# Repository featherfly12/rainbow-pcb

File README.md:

This is a pcb strip with rainbow leds! The part list is below and all the kicad files are listed\
you can buy assembled from vendor or try to solder it yourself!

## Parts List (BOM)

| Component | Value/Spec | Package | Qty |
|---|---|---|---|
| J1 — DC barrel jack | 5.5×2.1mm | THT | 1 |
| D1 — Protection diode | Schottky, SS14 | SOD-123 | 1 |
| SW1 — Switch | SPST, maintained | THT or SMD | 1 |
| LED — red | Vf ≈ 2.0V | 0805 | 13 |
| LED — orange | Vf ≈ 2.1V | 0805 | 13 |
| LED — yellow | Vf ≈ 2.1V | 0805 | 13 |
| LED — green | Vf ≈ 3.0V | 0805 | 13 |
| LED — blue | Vf ≈ 3.2V | 0805 | 13 |
| LED — purple | Vf ≈ 3.2V | 0805 | 13 |
| LED — pink | Vf ≈ 3.0-3.2V | 0805 | 13 |
| Resistor — 180Ω (red strings) | 180Ω | 0805 | 13 |
| Resistor — 160Ω (orange strings) | 160Ω | 0805 | 13 |
| Resistor — 160Ω (yellow strings) | 160Ω | 0805 | 13 |
| Resistor — 110Ω (green strings) | 110Ω | 0805 | 13 |
| Resistor — 100Ω (blue strings) | 100Ω | 0805 | 13 |
| Resistor — 100Ω (purple strings) | 100Ω | 0805 | 13 |
| Resistor — 100Ω (pink strings) | 100Ω | 0805 | 13 |
| Wall adapter | Regulated 5V/2A, center-positive | — | 1 |

**Total: 91 LEDs, 91 resistors, 1 jack, 1 diode, 1 switch**

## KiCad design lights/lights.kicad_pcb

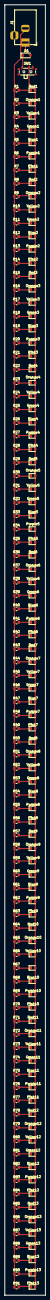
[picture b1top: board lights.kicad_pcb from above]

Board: 2 copper layers, 17.2 x 547.5 mm, 185 parts (0 on the bottom side), 95 nets.

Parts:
Blue1, Blue2, Blue3, Blue4, Blue5, Blue6, Blue7, Blue8, Blue9, Blue10, Blue11, Blue12, Blue13: LED; LED_0805_2012Metric
D1: D_Schottky; D_SOD-123
Green1, Green2, Green3, Green4, Green5, Green6, Green7, Green8, Green9, Green10, Green11, Green12, Green13: LED; LED_0805_2012Metric
J1: Barrel_Jack; BarrelJack_Horizontal
Orange1, Orange2, Orange3, Orange4, Orange5, Orange6, Orange7, Orange8, Orange9, Orange10, Orange11, Orange12, Orange13: LED; LED_0805_2012Metric
Pink1, Pink2, Pink3, Pink4, Pink5, Pink6, Pink7, Pink8, Pink9, Pink10, Pink11, Pink12, Pink13: LED; LED_0805_2012Metric
Purple1, Purple2, Purple3, Purple4, Purple5, Purple6, Purple7, Purple8, Purple9, Purple10, Purple11, Purple12, Purple13: LED; LED_0805_2012Metric
R1, R2, R3, R4, R5, R6, R7, R8, R9, R10, R11, R12, R13, R14, R15, R16, R17, R18, R19, R20, R21, R22, R23, R24, R25, R26, R27, R28, R29, R30, R31, R32, R33, R34, R35, R36, R37, R38, R39, R40, R41, R42, R43, R44, R45, R46, R47, R48, R49, R50, R51, R52, R53, R54, R55, R56, R57, R58, R59, R60, R61, R62, R63, R64, R65, R66, R67, R68, R69, R70, R71, R72, R73, R74, R75, R76, R77, R78, R79, R80, R81, R82, R83, R84, R85, R86, R87, R88, R89, R90, R91: R; R_0805_2012Metric
Red1, Red2, Red3, Red4, Red5, Red6, Red7, Red8, Red9, Red10, Red11, Red12, Red13: LED; LED_0805_2012Metric
SW1: SW_SPST; SW_SPDT_PCM12
Yellow1, Yellow2, Yellow3, Yellow4, Yellow5, Yellow6, Yellow7, Yellow8, Yellow9, Yellow10, Yellow11, Yellow12, Yellow13: LED; LED_0805_2012Metric

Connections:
/+5V: Blue1.2 (A), Blue2.2 (A), Blue3.2 (A), Blue4.2 (A), Blue5.2 (A), Blue6.2 (A), Blue7.2 (A), Blue8.2 (A), Blue9.2 (A), Blue10.2 (A), Blue11.2 (A), Blue12.2 (A), Blue13.2 (A), Green1.2 (A), Green2.2 (A), Green3.2 (A), Green4.2 (A), Green5.2 (A), Green6.2 (A), Green7.2 (A), Green8.2 (A), Green9.2 (A), Green10.2 (A), Green11.2 (A), Green12.2 (A), Green13.2 (A), Orange1.2 (A), Orange2.2 (A), Orange3.2 (A), Orange4.2 (A), Orange5.2 (A), Orange6.2 (A), Orange7.2 (A), Orange8.2 (A), Orange9.2 (A), Orange10.2 (A), Orange11.2 (A), Orange12.2 (A), Orange13.2 (A), Pink1.2 (A), Pink2.2 (A), Pink3.2 (A), Pink4.2 (A), Pink5.2 (A), Pink6.2 (A), Pink7.2 (A), Pink8.2 (A), Pink9.2 (A), Pink10.2 (A), Pink11.2 (A), Pink12.2 (A), Pink13.2 (A), Purple1.2 (A), Purple2.2 (A), Purple3.2 (A), Purple4.2 (A), Purple5.2 (A), Purple6.2 (A), Purple7.2 (A), Purple8.2 (A), Purple9.2 (A), Purple10.2 (A), Purple11.2 (A), Purple12.2 (A), Purple13.2 (A), Red1.2 (A), Red2.2 (A), Red3.2 (A), Red4.2 (A), Red5.2 (A), Red6.2 (A), Red7.2 (A), Red8.2 (A), Red9.2 (A), Red10.2 (A), Red11.2 (A), Red12.2 (A), Red13.2 (A), SW1.2 (B), Yellow1.2 (A), Yellow2.2 (A), Yellow3.2 (A), Yellow4.2 (A), Yellow5.2 (A), Yellow6.2 (A), Yellow7.2 (A), Yellow8.2 (A), Yellow9.2 (A), Yellow10.2 (A), Yellow11.2 (A), Yellow12.2 (A), Yellow13.2 (A)
GND: J1.2, R1.1, R2.1, R3.1, R4.1, R5.1, R6.1, R7.1, R8.1, R9.1, R10.1, R11.1, R12.1, R13.1, R14.1, R15.1, R16.1, R17.1, R18.1, R19.1, R20.1, R21.1, R22.1, R23.1, R24.1, R25.1, R26.1, R27.1, R28.1, R29.1, R30.1, R31.1, R32.1, R33.1, R34.1, R35.1, R36.1, R37.1, R38.1, R39.1, R40.1, R41.1, R42.1, R43.1, R44.1, R45.1, R46.1, R47.1, R48.1, R49.1, R50.1, R51.1, R52.1, R53.1, R54.1, R55.1, R56.1, R57.1, R58.1, R59.1, R60.1, R61.1, R62.1, R63.1, R64.1, R65.1, R66.1, R67.1, R68.1, R69.1, R70.1, R71.1, R72.1, R73.1, R74.1, R75.1, R76.1, R77.1, R78.1, R79.1, R80.1, R81.1, R82.1, R83.1, R84.1, R85.1, R86.1, R87.1, R88.1, R89.1, R90.1, R91.1
unnamed: Blue1.1 (K), R5.2
unnamed: Blue2.1 (K), R12.2
unnamed: Blue3.1 (K), R19.2
unnamed: Blue4.1 (K), R26.2
unnamed: Blue5.1 (K), R33.2
unnamed: Blue6.1 (K), R40.2
unnamed: Blue7.1 (K), R47.2
unnamed: Blue8.1 (K), R54.2
unnamed: Blue9.1 (K), R61.2
unnamed: Blue10.1 (K), R68.2
unnamed: Blue11.1 (K), R75.2
unnamed: Blue12.1 (K), R82.2
unnamed: Blue13.1 (K), R89.2
unnamed: D1.2 (A), J1.1
unnamed: D1.1 (K), SW1.1 (A)
unnamed: Green1.1 (K), R4.2
unnamed: Green2.1 (K), R11.2
unnamed: Green3.1 (K), R18.2
unnamed: Green4.1 (K), R25.2
unnamed: Green5.1 (K), R32.2
unnamed: Green6.1 (K), R39.2
unnamed: Green7.1 (K), R46.2
unnamed: Green8.1 (K), R53.2
unnamed: Green9.1 (K), R60.2
unnamed: Green10.1 (K), R67.2
unnamed: Green11.1 (K), R74.2
unnamed: Green12.1 (K), R81.2
unnamed: Green13.1 (K), R88.2
unnamed: Orange1.1 (K), R2.2
unnamed: Orange2.1 (K), R9.2
unnamed: Orange3.1 (K), R16.2
unnamed: Orange4.1 (K), R23.2
unnamed: Orange5.1 (K), R30.2
unnamed: Orange6.1 (K), R37.2
unnamed: Orange7.1 (K), R44.2
unnamed: Orange8.1 (K), R51.2
unnamed: Orange9.1 (K), R58.2
unnamed: Orange10.1 (K), R65.2
unnamed: Orange11.1 (K), R72.2
unnamed: Orange12.1 (K), R79.2
unnamed: Orange13.1 (K), R86.2
unnamed: Pink1.1 (K), R7.2
unnamed: Pink2.1 (K), R14.2
unnamed: Pink3.1 (K), R21.2
unnamed: Pink4.1 (K), R28.2
unnamed: Pink5.1 (K), R35.2
unnamed: Pink6.1 (K), R42.2
unnamed: Pink7.1 (K), R49.2
unnamed: Pink8.1 (K), R56.2
unnamed: Pink9.1 (K), R63.2
unnamed: Pink10.1 (K), R70.2
unnamed: Pink11.1 (K), R77.2
unnamed: Pink12.1 (K), R84.2
unnamed: Pink13.1 (K), R91.2
unnamed: Purple1.1 (K), R6.2
unnamed: Purple2.1 (K), R13.2
unnamed: Purple3.1 (K), R20.2
unnamed: Purple4.1 (K), R27.2
unnamed: Purple5.1 (K), R34.2
unnamed: Purple6.1 (K), R41.2
unnamed: Purple7.1 (K), R48.2
unnamed: Purple8.1 (K), R55.2
unnamed: Purple9.1 (K), R62.2
unnamed: Purple10.1 (K), R69.2
unnamed: Purple11.1 (K), R76.2
unnamed: Purple12.1 (K), R83.2
unnamed: Purple13.1 (K), R90.2
unnamed: R1.2, Red1.1 (K)
unnamed: R8.2, Red2.1 (K)
unnamed: R15.2, Red3.1 (K)
unnamed: R22.2, Red4.1 (K)
unnamed: R29.2, Red5.1 (K)
unnamed: R36.2, Red6.1 (K)
unnamed: R43.2, Red7.1 (K)
unnamed: R50.2, Red8.1 (K)
unnamed: R57.2, Red9.1 (K)
unnamed: R64.2, Red10.1 (K)
unnamed: R71.2, Red11.1 (K)
unnamed: R78.2, Red12.1 (K)
unnamed: R85.2, Red13.1 (K)
unnamed: R3.2, Yellow1.1 (K)
unnamed: R10.2, Yellow2.1 (K)
unnamed: R17.2, Yellow3.1 (K)
unnamed: R24.2, Yellow4.1 (K)
unnamed: R31.2, Yellow5.1 (K)
unnamed: R38.2, Yellow6.1 (K)
unnamed: R45.2, Yellow7.1 (K)
unnamed: R52.2, Yellow8.1 (K)
unnamed: R59.2, Yellow9.1 (K)
unnamed: R66.2, Yellow10.1 (K)
unnamed: R73.2, Yellow11.1 (K)
unnamed: R80.2, Yellow12.1 (K)
unnamed: R87.2, Yellow13.1 (K)

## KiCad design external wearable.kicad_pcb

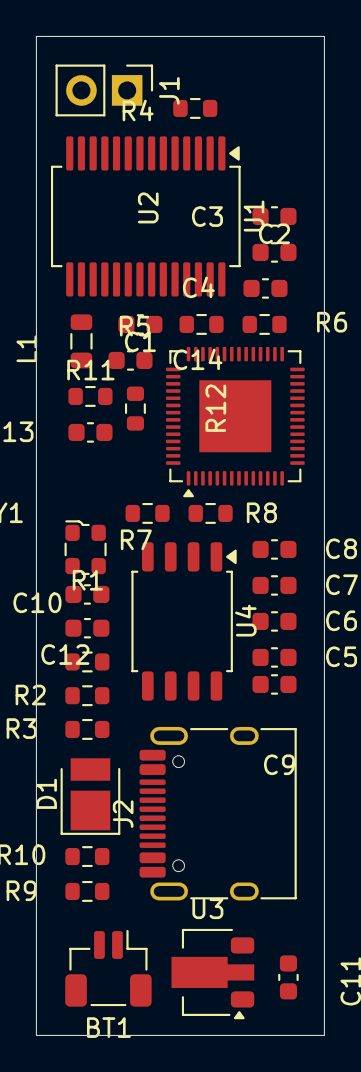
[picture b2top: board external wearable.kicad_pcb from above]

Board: 2 copper layers, 16.0 x 55.5 mm, 36 parts (0 on the bottom side), 33 nets, no tracks yet.

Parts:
BT1: Battery_Cell; JST_SH_BM02B-SRSS-TB_1x02-1MP_P1.00mm_Vertical
C1, C2, C3, C4, C5, C6, C7, C8, C9, C10, C11, C12, C13, C14: C; C_0603_1608Metric
D1: LED_ARGB; LED_PLCC_2835
J1: Conn_01x02; PinHeader_1x02_P2.54mm_Vertical
J2: USB_C_Receptacle; USB_C_Receptacle_HRO_TYPE-C-31-M-12
L1: L; L_0805_2012Metric
R1, R2, R3, R4, R5, R6, R7, R8, R9, R10, R11, R12: R; R_0603_1608Metric
U1: AD9850; SSOP-28_5.3x10.2mm_P0.65mm
U2: ESP32-S3; QFN-56-1EP_7x7mm_P0.4mm_EP4x4mm
U3: MCP1700x-330xxMB; SOT-89-3
U4: W25Q32JVSS; SOIC-8_5.3x5.3mm_P1.27mm
Y1: ECS-2520MV-xxx-xx; Oscillator_SMD_ECS_2520MV-xxx-xx-4Pin_2.5x2.0mm

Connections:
/+3.3v: C2.2, C3.2, C4.2, C5.2, C6.2, C7.2, C8.2, C9.2, C10.2, C11.2, C12.1, R7.2, R8.2, R12.1, U1.6 (DVDD), U1.11 (AVDD), U1.18 (AVDD), U1.23 (DVDD), U2.2 (VDD3P3), U2.3 (VDD3P3), U2.20 (VDD3P3_RTC), U2.29 (VDD_SPI), U2.46 (VDD3P3_CPU), U2.55 (VDDA), U2.56 (VDDA), U3.3 (VO), U4.8 (VCC), Y1.1 (Tri-State), Y1.4 (VDD)
GND: BT1.2 (-), C1.1, C2.1, C3.1, C4.1, C5.1, C6.1, C7.1, C8.1, C9.1, C10.1, C11.1, C12.2, C13.1, D1.1 (A), J2.A1 (GND), J2.A12 (GND), J2.B1 (GND), J2.B12 (GND), L1.1, R4.1, R5.1, R6.1, R9.2, R10.2, R11.1, U1.1 (D3), U1.2 (D2), U1.3 (D1), U1.4 (D0), U1.5 (DGND), U1.10 (AGND), U1.19 (AGND), U1.24 (DGND), U1.26 (D6), U1.27 (D5), U1.28 (D4), U2.57 (GND), U3.1 (GND), U4.4 (GND), Y1.2 (GND)
unnamed: BT1.1 (+), U3.2 (VI)
unnamed: C14.1, L1.2
unnamed: D1.2 (RK), R3.1
unnamed: J1.1, U1.13 (QOUTB)
unnamed: J1.2, U1.14 (QOUT)
unnamed: J2.A5 (CC1), R10.1
unnamed: J2.B5 (CC2), R9.1
unnamed: U1.9 (CLKIN), Y1.3 (OUT)
unnamed: U1.25 (D7), U2.12 (GPIO7)
unnamed: C1.2, U1.17 (DACBL)
unnamed: U1.8 (FQ_UD), U2.10 (GPIO5)
unnamed: R6.2, U1.21 (IOUT)
unnamed: R5.2, U1.20 (IOUTB)
unnamed: U1.22 (RESET), U2.9 (GPIO4)
unnamed: R4.2, U1.12 (RSET)
unnamed: C13.2, R11.2, R12.2, U1.15 (VINN)
unnamed: C14.2, U1.16 (VINP)
unnamed: U1.7 (W_CLK), U2.11 (GPIO6)
unnamed: R7.1, U2.4 (CHIP_PU)
unnamed: R8.1, U2.5 (GPIO0)
unnamed: R1.2, U2.14 (GPIO9)
unnamed: R2.2, U2.15 (GPIO10)
unnamed: R3.2, U2.16 (GPIO11)
unnamed: J2.A7 (D-), J2.B7 (D-), U2.25 (GPIO19/USB_D-)
unnamed: J2.A6 (D+), J2.B6 (D+), U2.26 (GPIO20/USB_D+)
unnamed: U2.33 (SPICLK), U4.6 (CLK)
unnamed: U2.36 (SPICLK_N), U4.7 (~HOLD/~RESET/IO_{3})
unnamed: U2.32 (SPICS0), U4.1 (~CS)
unnamed: U2.35 (SPID), U4.5 (DI/IO_{0})
unnamed: U2.34 (SPIQ), U4.2 (DO/IO_{1})
unnamed: U2.31 (SPIWP), U4.3 (~WP/IO_{2})
